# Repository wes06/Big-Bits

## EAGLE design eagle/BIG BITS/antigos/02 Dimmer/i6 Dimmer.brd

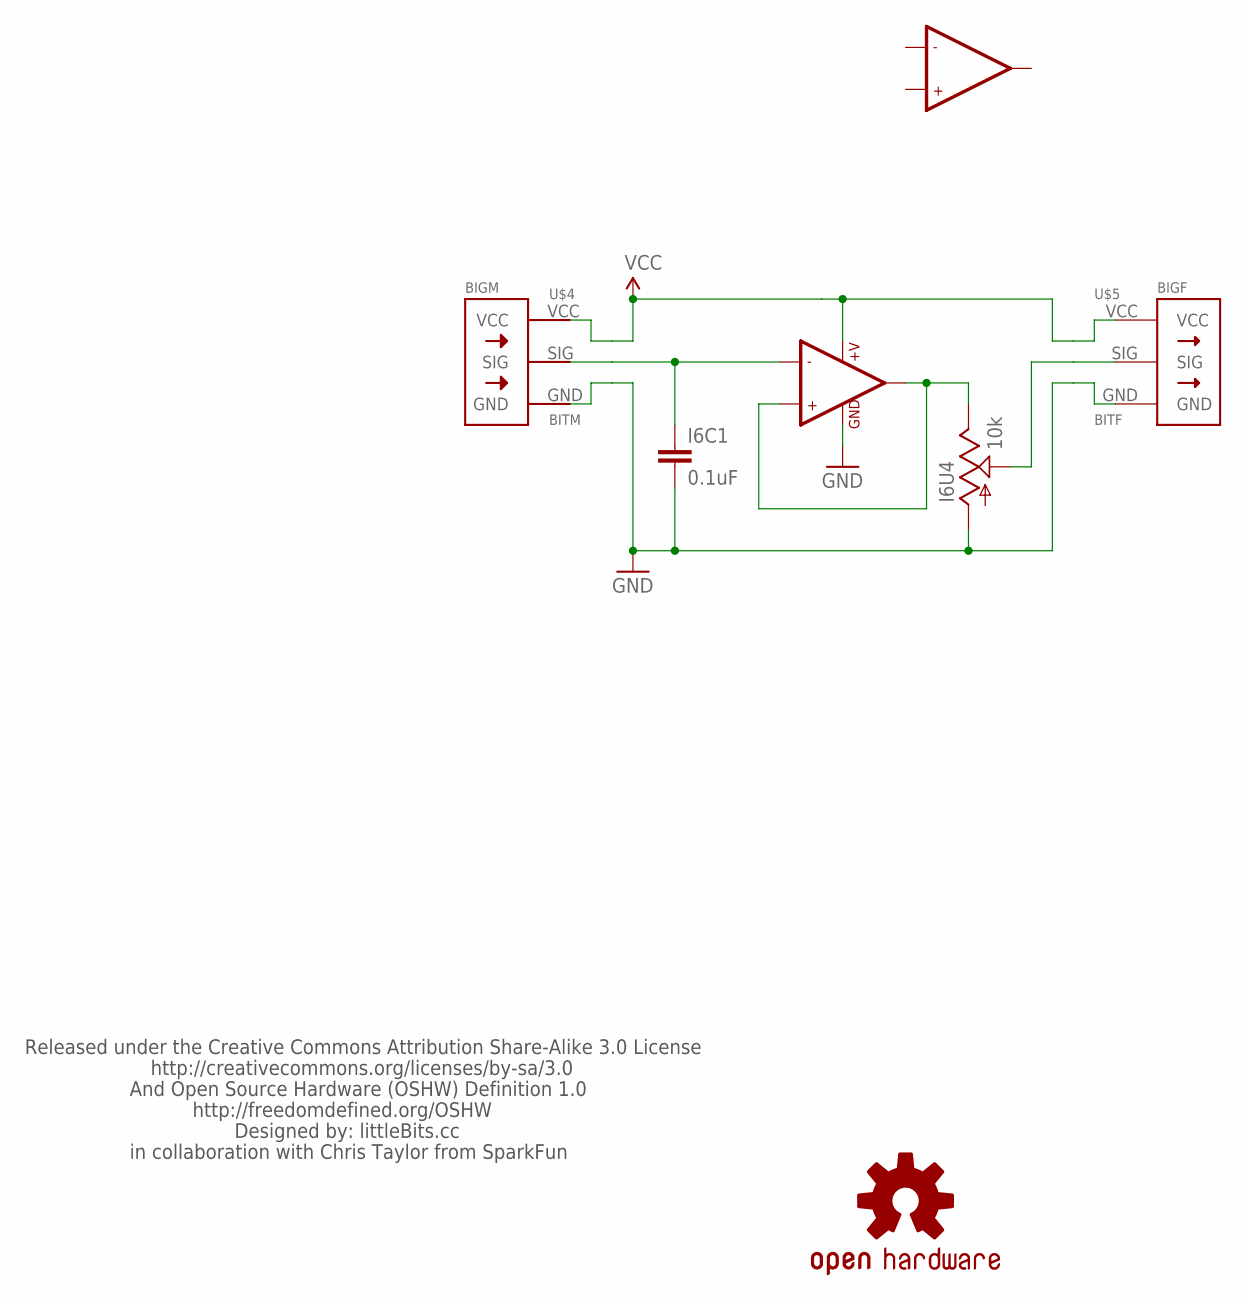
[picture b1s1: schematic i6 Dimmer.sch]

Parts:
I6C1: 0.1uF; 1206
I6U4: 10k; ALPS_POT
U$1: LB_CREDITS; OSHWCREDIT
U$2: LMV358; SO08
U$3: OSHW-LOGOL; OSHW-LOGO-L
U$4: BITM
U$5: BITF; BITM

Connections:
GND: I6C1.2, I6U4.P$3 (A), U$2.4 (GND), U$4.GND, U$5.GND
unnamed: I6U4.P$1 (E), U$2.1 (OUT1), U$2.3 (+IN1)
POT: I6U4.P$2 (S), U$5.SIG
SIG: I6C1.1, U$2.2 (-IN1), U$4.SIG
VCC: U$2.8 (+V), U$4.VCC, U$5.VCC

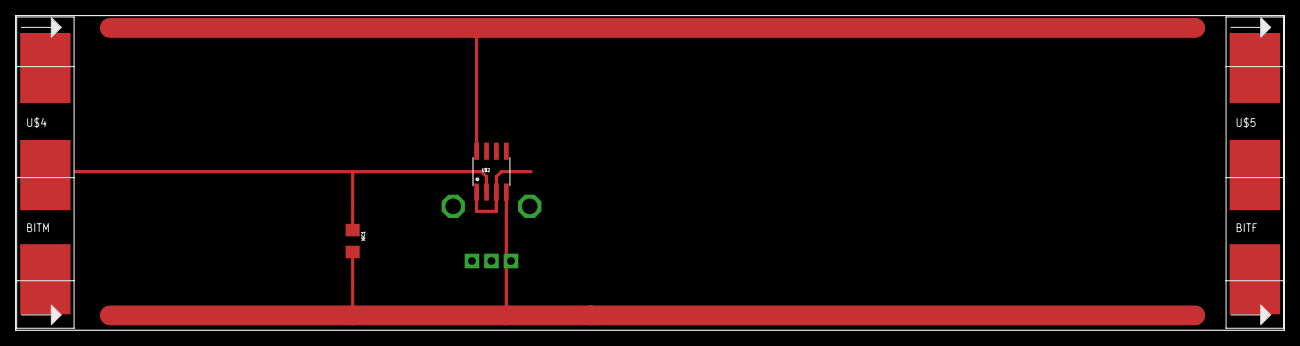
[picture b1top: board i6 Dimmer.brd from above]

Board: 2 copper layers, 162.5 x 40.3 mm, 7 parts (0 on the bottom side), 5 nets.

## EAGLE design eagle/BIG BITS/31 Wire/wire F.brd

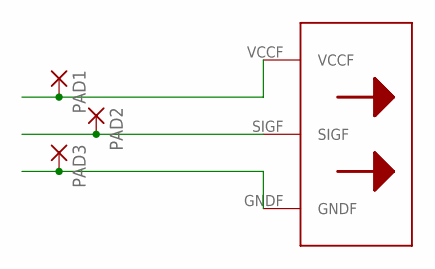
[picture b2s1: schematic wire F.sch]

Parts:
PAD1, PAD2, PAD3: SMD5; SMD2,54-5,08
U$2: BITWIREF

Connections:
unnamed: PAD1.1, U$2.VCCF
unnamed: PAD2.1, U$2.SIGF
unnamed: PAD3.1, U$2.GNDF

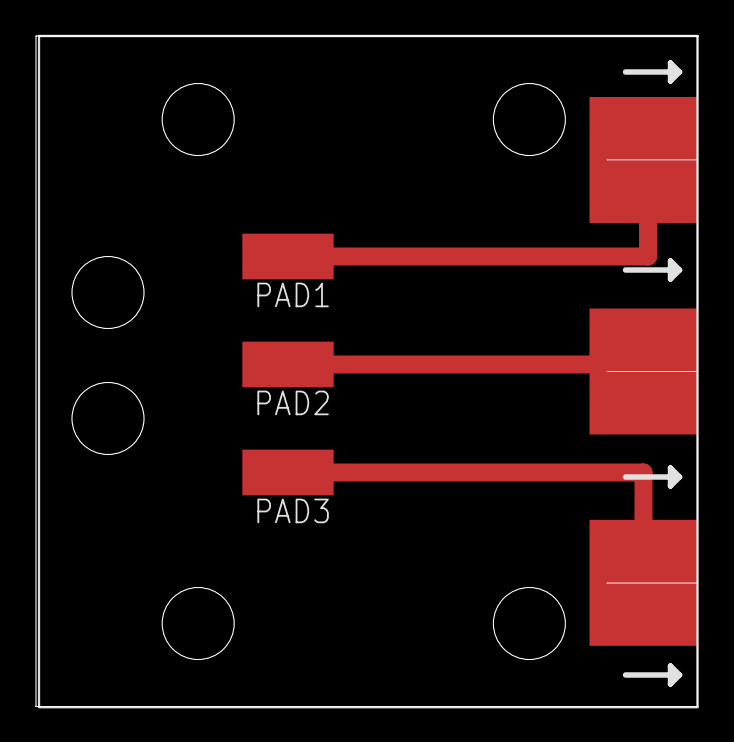
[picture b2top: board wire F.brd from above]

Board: 2 copper layers, 36.8 x 37.2 mm, 4 parts (0 on the bottom side), 3 nets.

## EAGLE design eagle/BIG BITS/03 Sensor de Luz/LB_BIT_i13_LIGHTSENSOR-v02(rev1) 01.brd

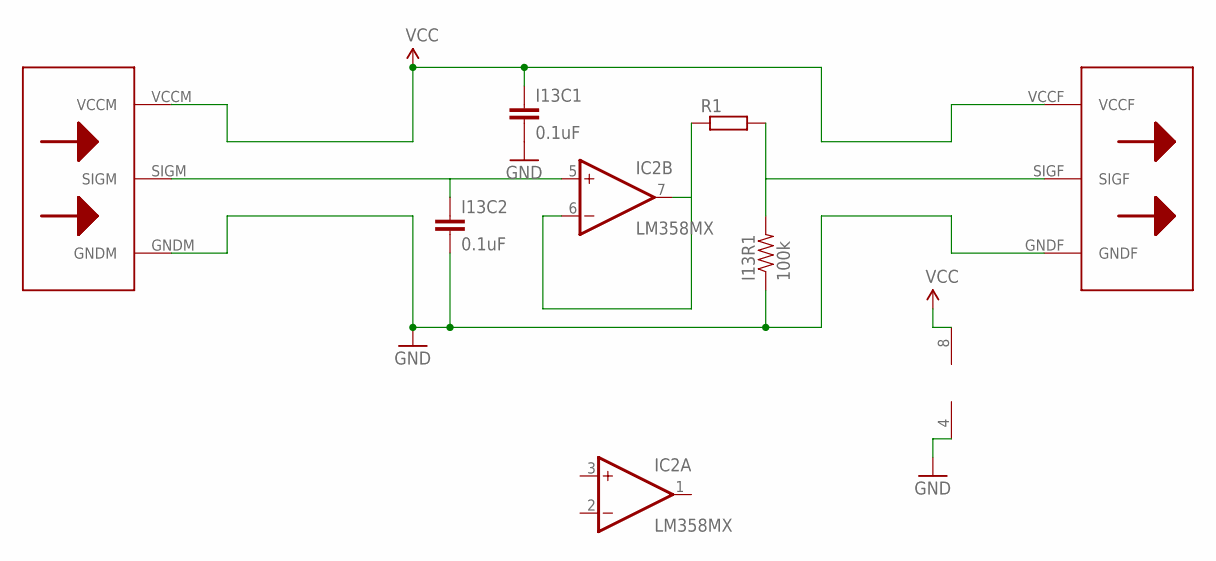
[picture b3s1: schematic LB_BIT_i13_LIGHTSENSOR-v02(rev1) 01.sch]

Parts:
I13C1, I13C2: 0.1uF; 1206
I13R1: 100k; 0805
IC2: LM358MX; SO08
R1: R-EU_R2512; R2512
U$1: BIGBIT

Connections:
GND: I13C1.2, I13C2.2, I13R1.1, IC2.4 (V-), U$1.GNDF, U$1.GNDM
unnamed: IC2.6 (-IN), IC2.7 (OUT), R1.1
PS: I13R1.2, R1.2, U$1.SIGF
SIG: I13C2.1, IC2.5 (+IN), U$1.SIGM
VCC: I13C1.1, IC2.8 (V+), U$1.VCCF, U$1.VCCM

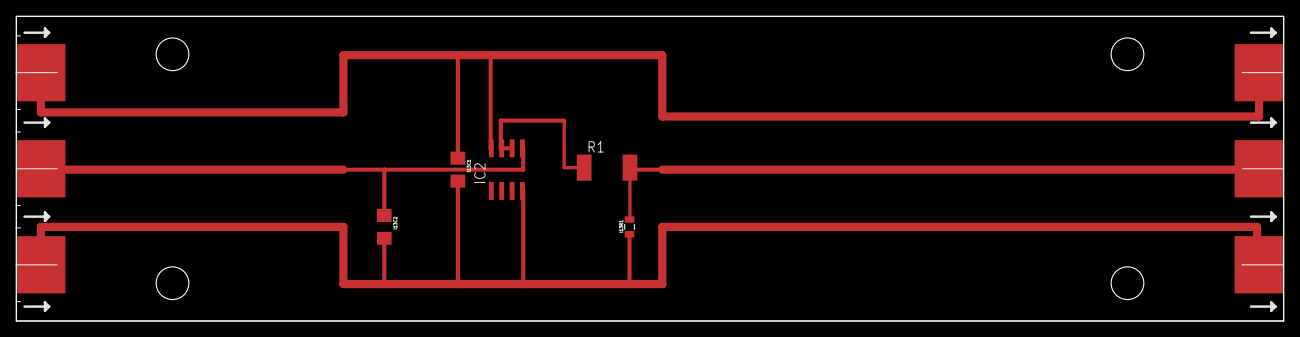
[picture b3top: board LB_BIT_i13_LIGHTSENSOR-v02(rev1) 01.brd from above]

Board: 2 copper layers, 155.0 x 37.2 mm, 6 parts (0 on the bottom side), 5 nets.

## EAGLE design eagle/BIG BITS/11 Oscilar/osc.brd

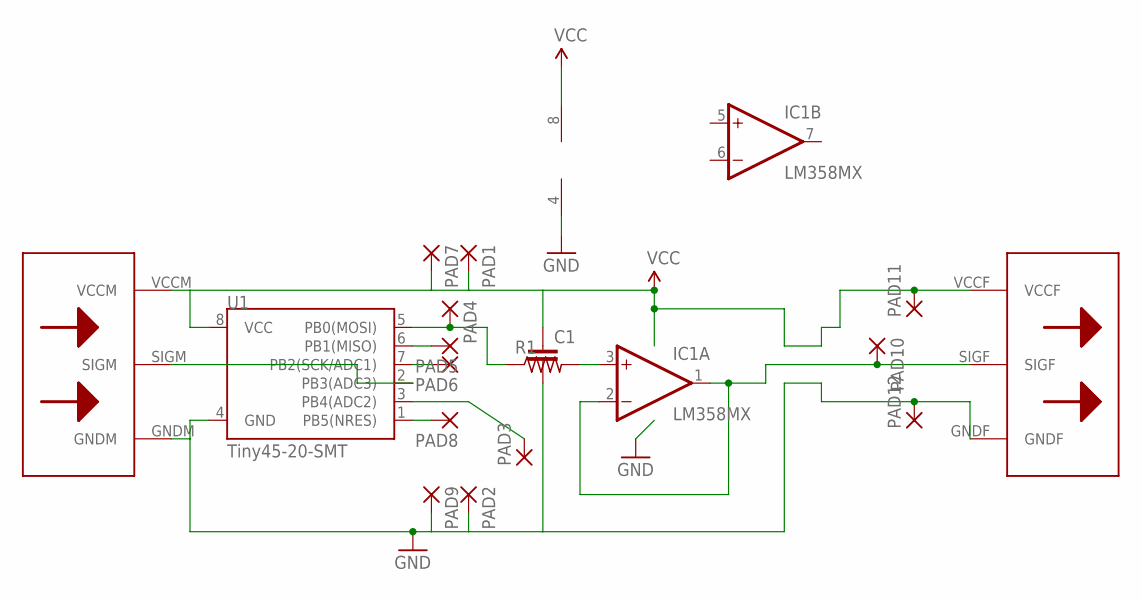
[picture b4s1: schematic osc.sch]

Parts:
C1: C-EUC1206K; C1206K
IC1: LM358MX; SO08
PAD1, PAD2, PAD3, PAD4, PAD5, PAD6, PAD7, PAD8, PAD9, PAD10, PAD11, PAD12: SMD2; SMD1,27-2,54
R1: R-US_R0805; R0805
U1: Tiny45-20-SMT; SO08-EIAJ
U$6: BIGBIT

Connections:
GND: C1.2, IC1.4 (V-), PAD2.1, PAD9.1, PAD12.1, U1.4 (GND), U$6.GNDF, U$6.GNDM
unnamed: PAD4.1, R1.1, U1.5 (PB0(MOSI))
unnamed: U1.2 (PB3(ADC3)), U$6.SIGM
unnamed: IC1.3 (+IN), R1.2
unnamed: PAD3.1, U1.3 (PB4(ADC2))
unnamed: PAD8.1, U1.1 (PB5(NRES))
unnamed: PAD6.1, U1.7 (PB2(SCK/ADC1))
unnamed: PAD5.1, U1.6 (PB1(MISO))
POT: IC1.1 (OUT), IC1.2 (-IN), PAD10.1, U$6.SIGF
VCC: C1.1, IC1.8 (V+), PAD1.1, PAD7.1, PAD11.1, U1.8 (VCC), U$6.VCCF, U$6.VCCM

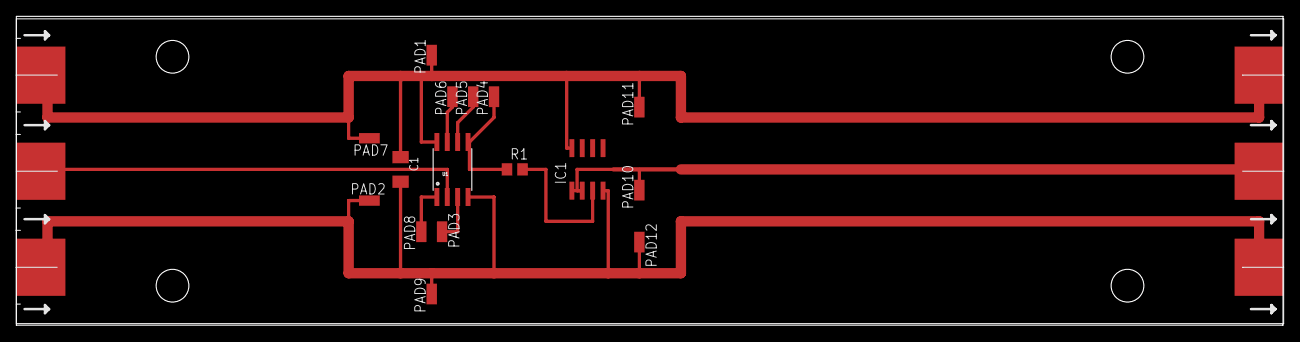
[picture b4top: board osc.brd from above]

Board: 2 copper layers, 154.9 x 37.8 mm, 17 parts (0 on the bottom side), 10 nets.

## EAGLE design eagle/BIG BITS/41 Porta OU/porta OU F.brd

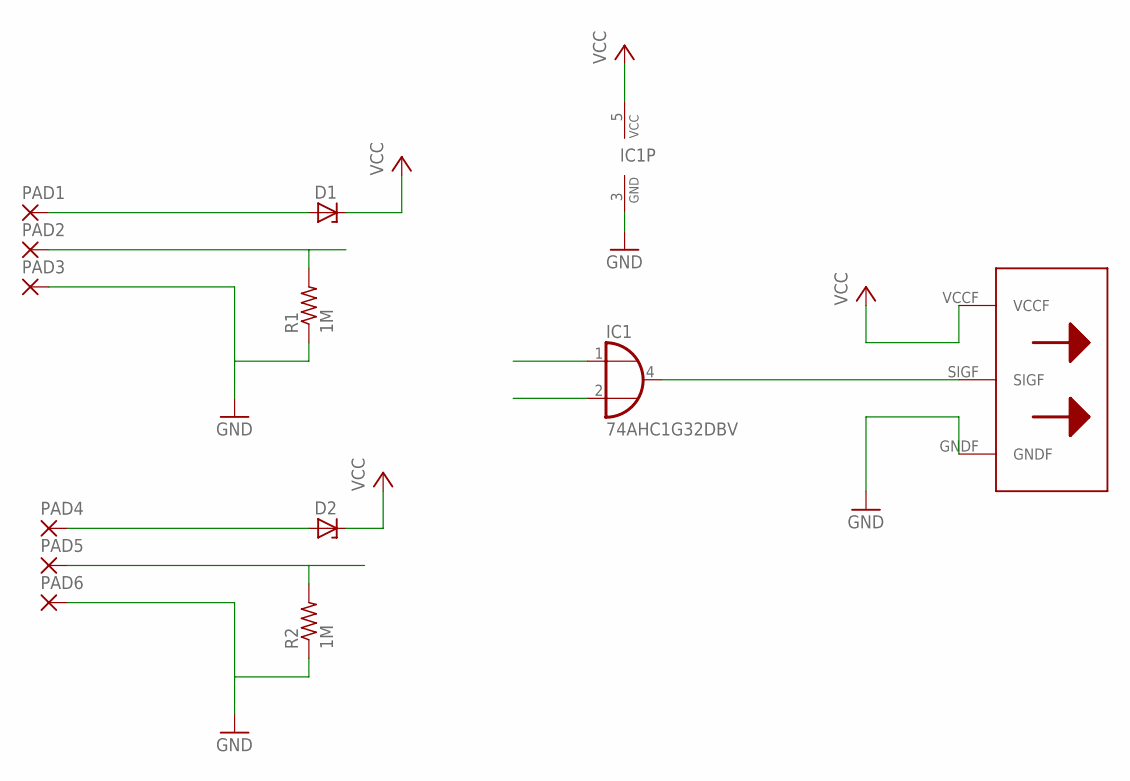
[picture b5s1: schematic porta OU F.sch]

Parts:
D1, D2: ZENER-DIODESOD80C; SOD80C
IC1: 74AHC1G32DBV; SOT23-5
PAD1, PAD2, PAD3, PAD4, PAD5, PAD6: SMD5; SMD2,54-5,08
R1, R2: 1M; M0805
U$2: BITWIREF

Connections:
unnamed: D1.A, PAD1.1
unnamed: D2.A, PAD4.1
unnamed: IC1.3 (GND), PAD3.1, PAD6.1, R1.1, R2.1, U$2.GNDF
unnamed: IC1.4 (O), U$2.SIGF
SIG1: IC1.1 (I0), PAD2.1, R1.2
SIG2: IC1.2 (I1), PAD5.1, R2.2
VCC: D1.C, D2.C, IC1.5 (VCC), U$2.VCCF

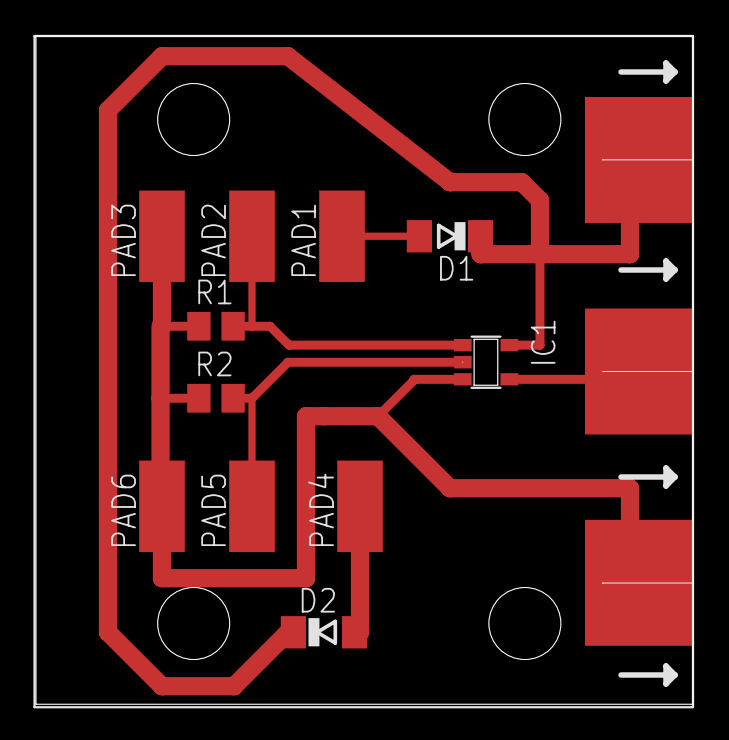
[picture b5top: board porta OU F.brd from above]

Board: 2 copper layers, 36.5 x 37.1 mm, 12 parts (0 on the bottom side), 7 nets.

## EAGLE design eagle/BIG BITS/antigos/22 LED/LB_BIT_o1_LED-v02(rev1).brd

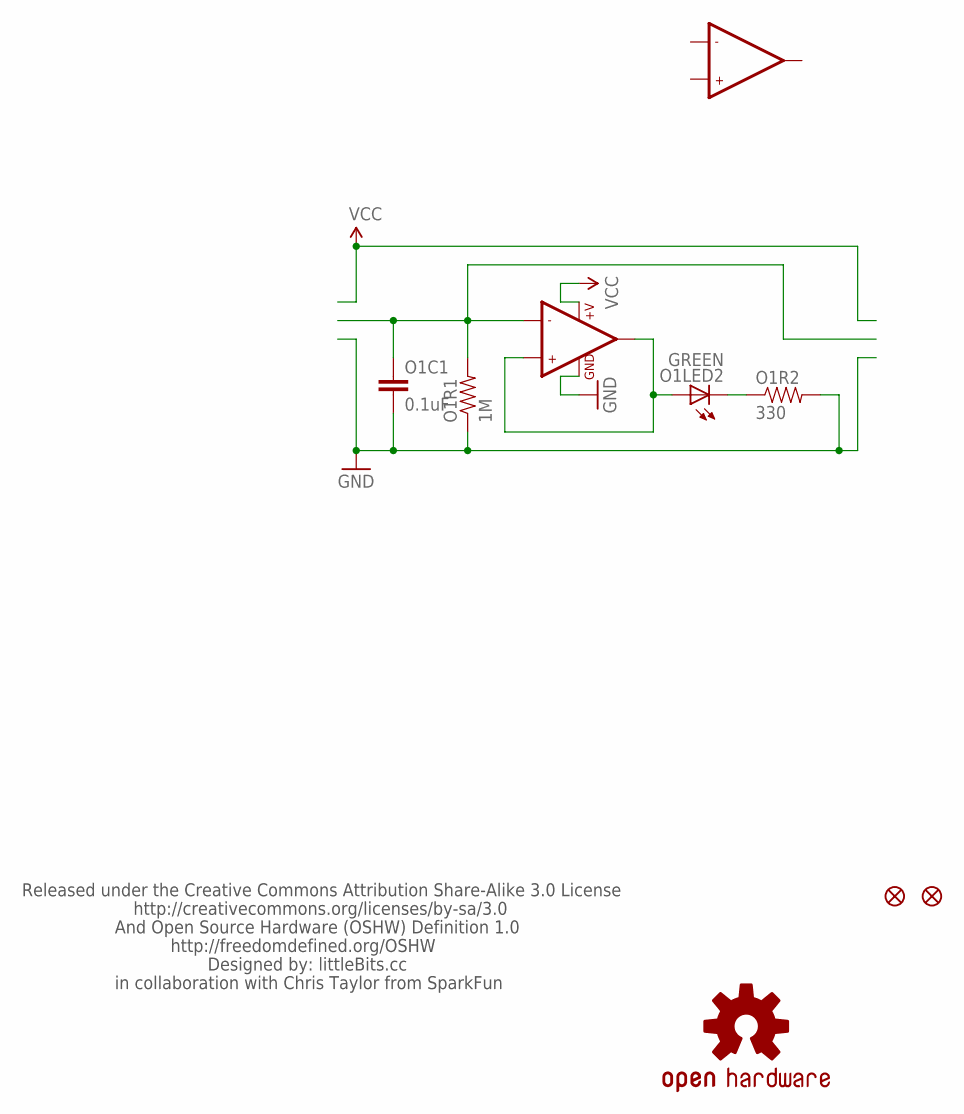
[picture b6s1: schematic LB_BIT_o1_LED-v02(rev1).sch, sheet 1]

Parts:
JP1, JP2: FIDUCIAL1X2.5; FIDUCIAL-1X2.5
O1C1: 0.1uF; 1206
O1LED2: GREEN; LED-1206
O1R1: 1M; 0805
O1R2: 330; 0805
U$1: LB_CREDITS; OSHWCREDIT
U$3: OSHW-LOGOL; OSHW-LOGO-L
U$7: LMV358; SO08

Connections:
GND: O1C1.2, O1R1.1, O1R2.2, U$7.4 (GND); also elsewhere on the board
LEDGND: O1LED2.C, O1R2.1
unnamed: O1LED2.A, U$7.1 (OUT1), U$7.3 (+IN1)
SIG: O1C1.1, O1R1.2, U$7.2 (-IN1); also elsewhere on the board
VCC: U$7.8 (+V); also elsewhere on the board

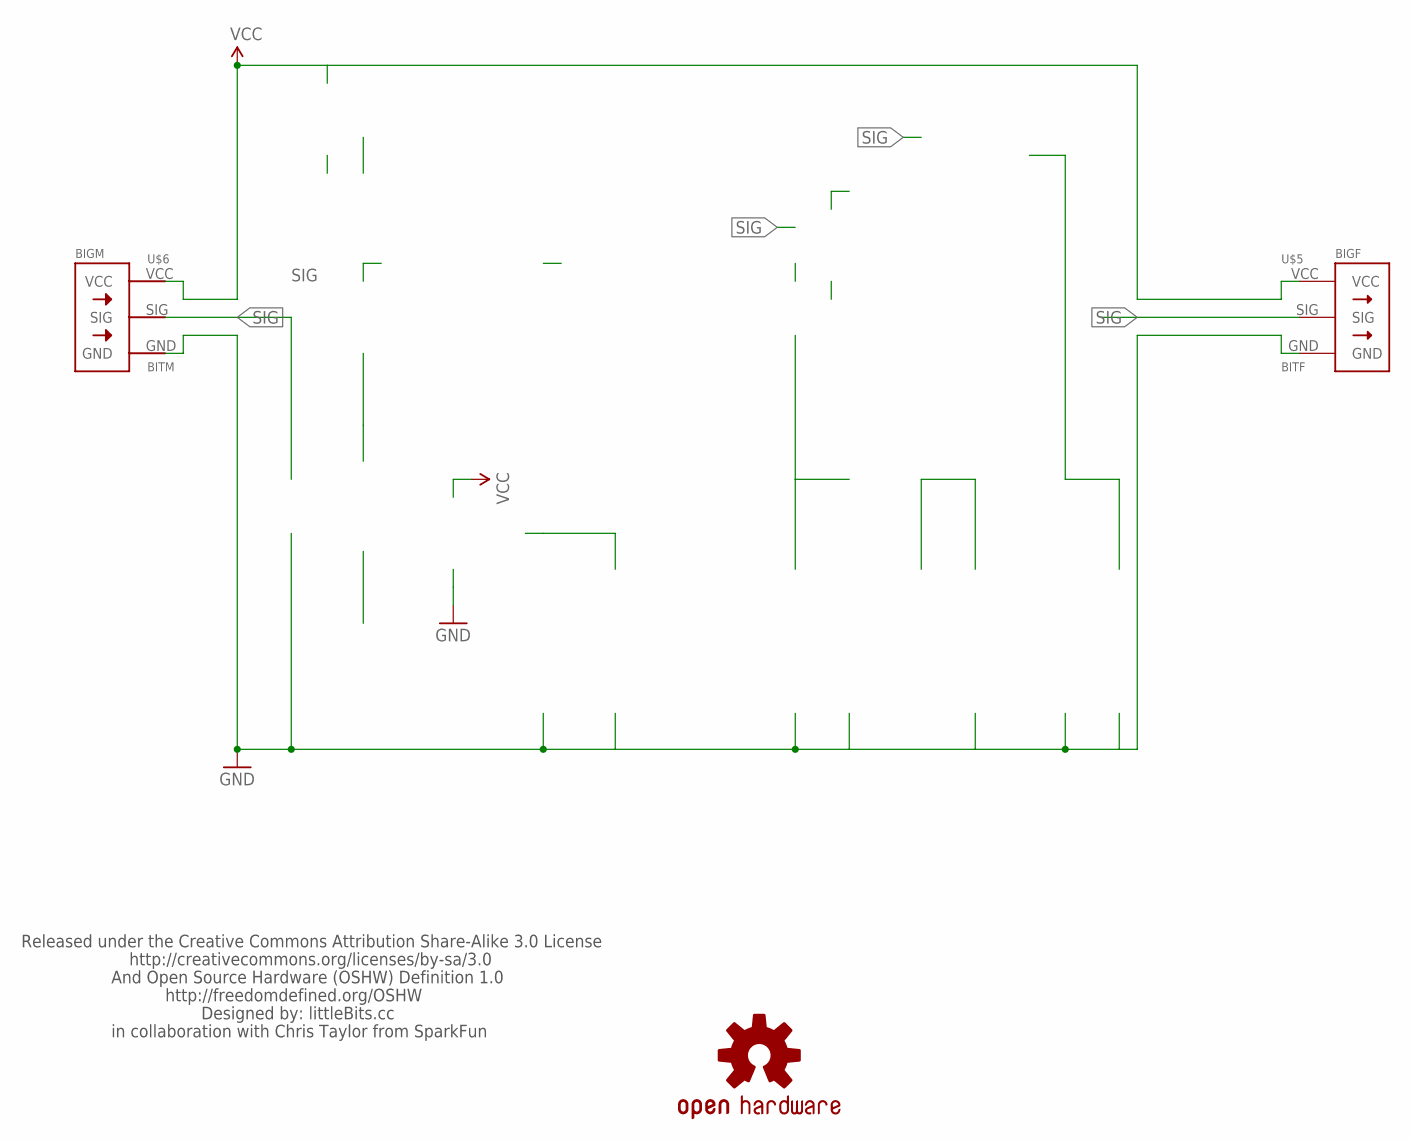
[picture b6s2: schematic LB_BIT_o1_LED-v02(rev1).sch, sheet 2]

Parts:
U$2: OSHW-LOGOL; OSHW-LOGO-L
U$4: LB_CREDITS; OSHWCREDIT
U$5: BITF; BITM
U$6: BITM

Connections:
GND: U$5.GND, U$6.GND; also elsewhere on the board
SIG: U$5.SIG, U$6.SIG; also elsewhere on the board
VCC: U$5.VCC, U$6.VCC; also elsewhere on the board

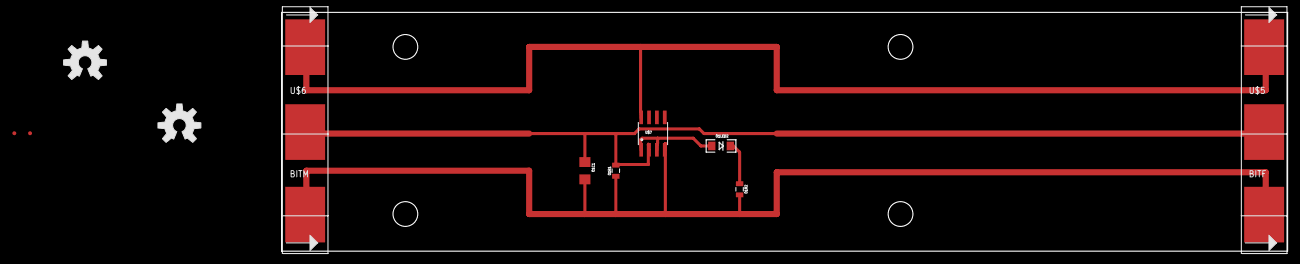
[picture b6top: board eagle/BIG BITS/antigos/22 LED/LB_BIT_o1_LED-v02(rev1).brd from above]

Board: 2 copper layers, 162.5 x 38.6 mm, 13 parts (0 on the bottom side), 5 nets.

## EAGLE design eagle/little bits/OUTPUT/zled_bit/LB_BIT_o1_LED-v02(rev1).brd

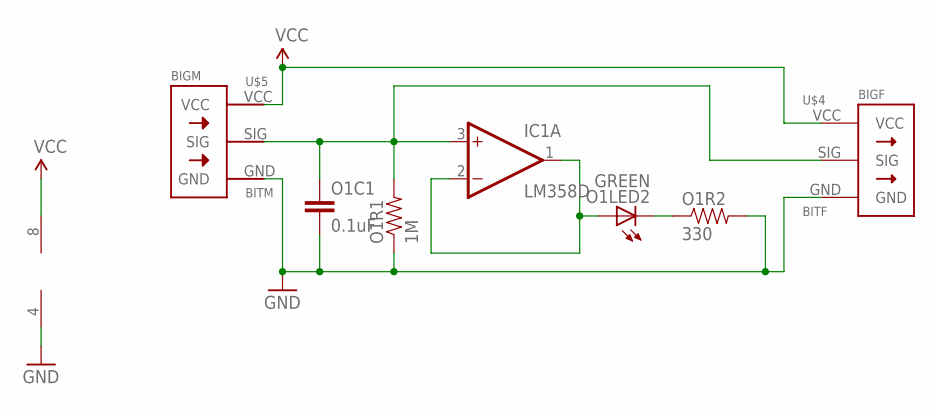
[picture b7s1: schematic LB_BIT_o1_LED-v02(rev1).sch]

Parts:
IC1: LM358D; SO08
O1C1: 0.1uF; 1206
O1LED2: GREEN; LED10MM
O1R1: 1M; 0805
O1R2: 330; 0805
U$4: BITF; BITM
U$5: BITM

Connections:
GND: IC1.4 (V-), O1C1.2, O1R1.1, O1R2.2, U$4.GND, U$5.GND
LEDGND: O1LED2.C, O1R2.1
unnamed: IC1.1 (OUT), IC1.2 (-IN), O1LED2.A
SIG: IC1.3 (+IN), O1C1.1, O1R1.2, U$4.SIG, U$5.SIG
VCC: IC1.8 (V+), U$4.VCC, U$5.VCC

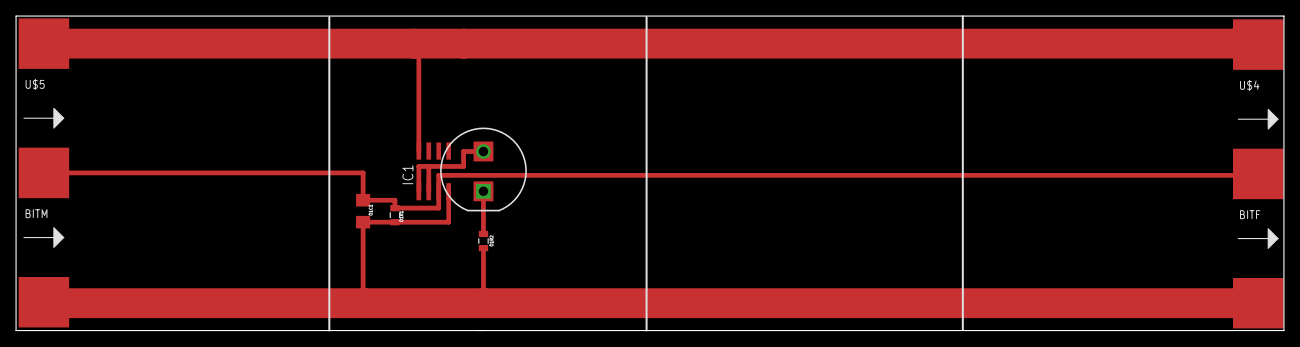
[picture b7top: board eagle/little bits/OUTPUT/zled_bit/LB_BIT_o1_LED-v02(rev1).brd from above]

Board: 2 copper layers, 161.9 x 40.2 mm, 7 parts (0 on the bottom side), 5 nets.

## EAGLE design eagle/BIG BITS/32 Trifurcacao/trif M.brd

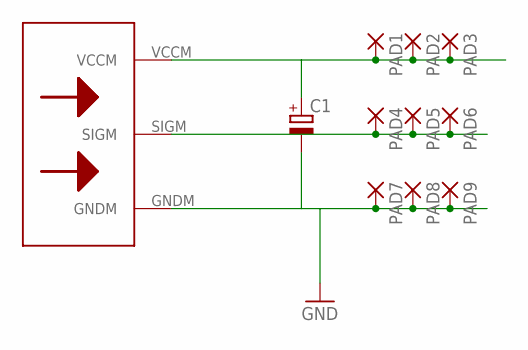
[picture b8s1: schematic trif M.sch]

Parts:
C1: CPOL-EU153CLV-1012; 153CLV-1012
PAD1, PAD2, PAD3, PAD4, PAD5, PAD6, PAD7, PAD8, PAD9: SMD2; SMD1,27-2,54
U$1: BITWIREM

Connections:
unnamed: PAD4.1, PAD5.1, PAD6.1, U$1.SIGM
unnamed: C1.+, PAD1.1, PAD2.1, PAD3.1, U$1.VCCM
unnamed: C1.-, PAD7.1, PAD8.1, PAD9.1, U$1.GNDM

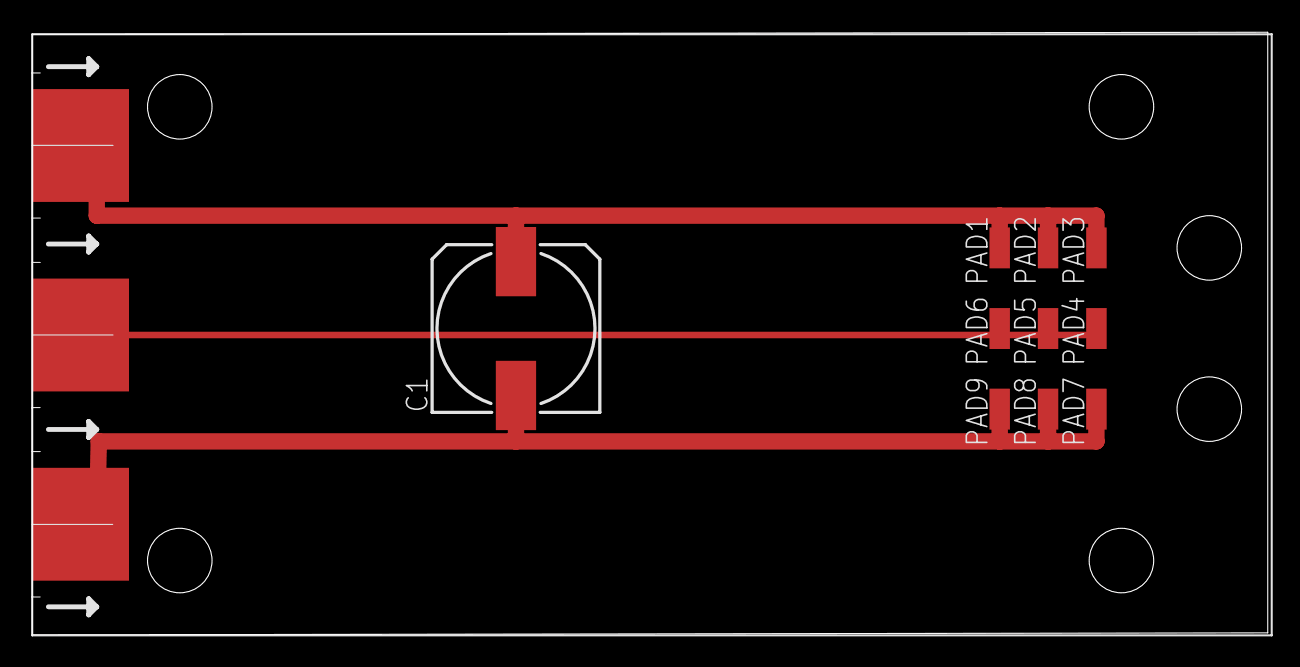
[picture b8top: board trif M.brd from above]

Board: 2 copper layers, 76.6 x 37.4 mm, 11 parts (0 on the bottom side), 3 nets.

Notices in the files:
parts and their libraries:
LITTLEBITS: Released under the Creative Commons Attribution Share-Alike 3.0 License
LITTLEBITS: http://creativecommons.org/license/by-sa/3.0
LITTLEBITS: http://creativecommons.org/licenses/by-sa/3.0
